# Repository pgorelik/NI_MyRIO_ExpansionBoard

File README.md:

# NI_MyRIO_ExpansionBoard
Breakout board with lick detection, solenoid driving and lights

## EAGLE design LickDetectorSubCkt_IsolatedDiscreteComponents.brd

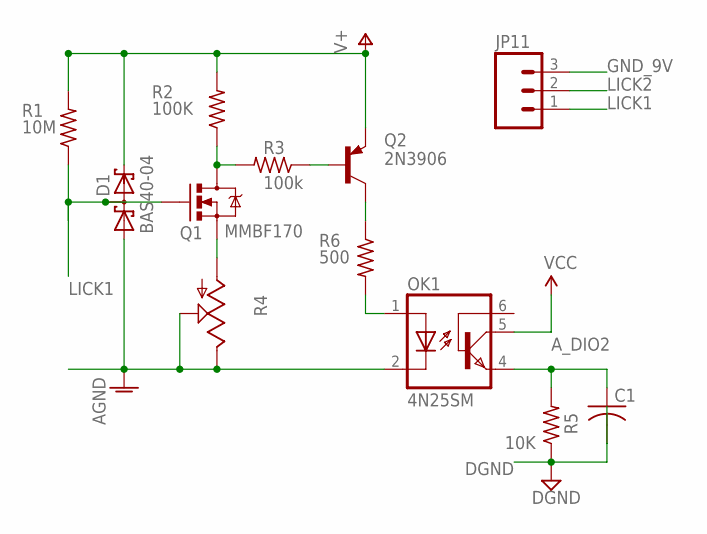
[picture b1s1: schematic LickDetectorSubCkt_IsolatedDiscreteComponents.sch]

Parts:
C1: C-US025-024X044; C025-024X044
D1: BAS40-04; SOT23
JP11: M03POLAR; MOLEX-1X3
OK1: 4N25SM; DIL6-SMD
Q1: MMBF170; SOT23-3
Q2: 2N3906; SOT23-BEC
R1: 10M; 0805S
R2: 100K; 0805S
R3: 100k; 0805S
R4: TRIM_US-B25P; B25P
R5: 10K; 0805S
R6: 500; 0805S

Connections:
AGND: D1.1 (A1), OK1.2 (C), R4.E, R4.S
A_DIO2: C1.1, OK1.4 (EMI), R5.2
DGND: C1.2, R5.1
GND_9V: JP11.3
LICK1: D1.3 (C1A2), JP11.1, Q1.1 (G), R1.1
LICK2: JP11.2
unnamed: Q1.2 (S), R4.A
unnamed: Q1.3 (D), R2.1, R3.2
unnamed: Q2.B, R3.1
unnamed: OK1.1 (A), R6.2
unnamed: Q2.C, R6.1
V+: D1.2 (C2), Q2.E, R1.2, R2.2
VCC: OK1.5 (COL)

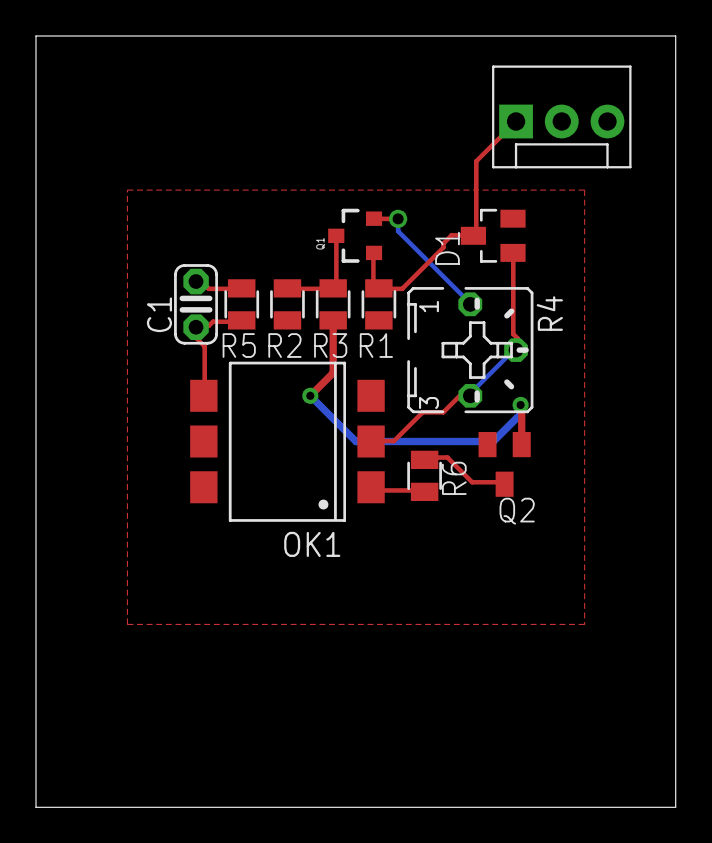
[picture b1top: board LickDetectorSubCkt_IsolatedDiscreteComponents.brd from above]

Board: 2 copper layers, 35.5 x 42.9 mm, 12 parts (0 on the bottom side), 10 nets.

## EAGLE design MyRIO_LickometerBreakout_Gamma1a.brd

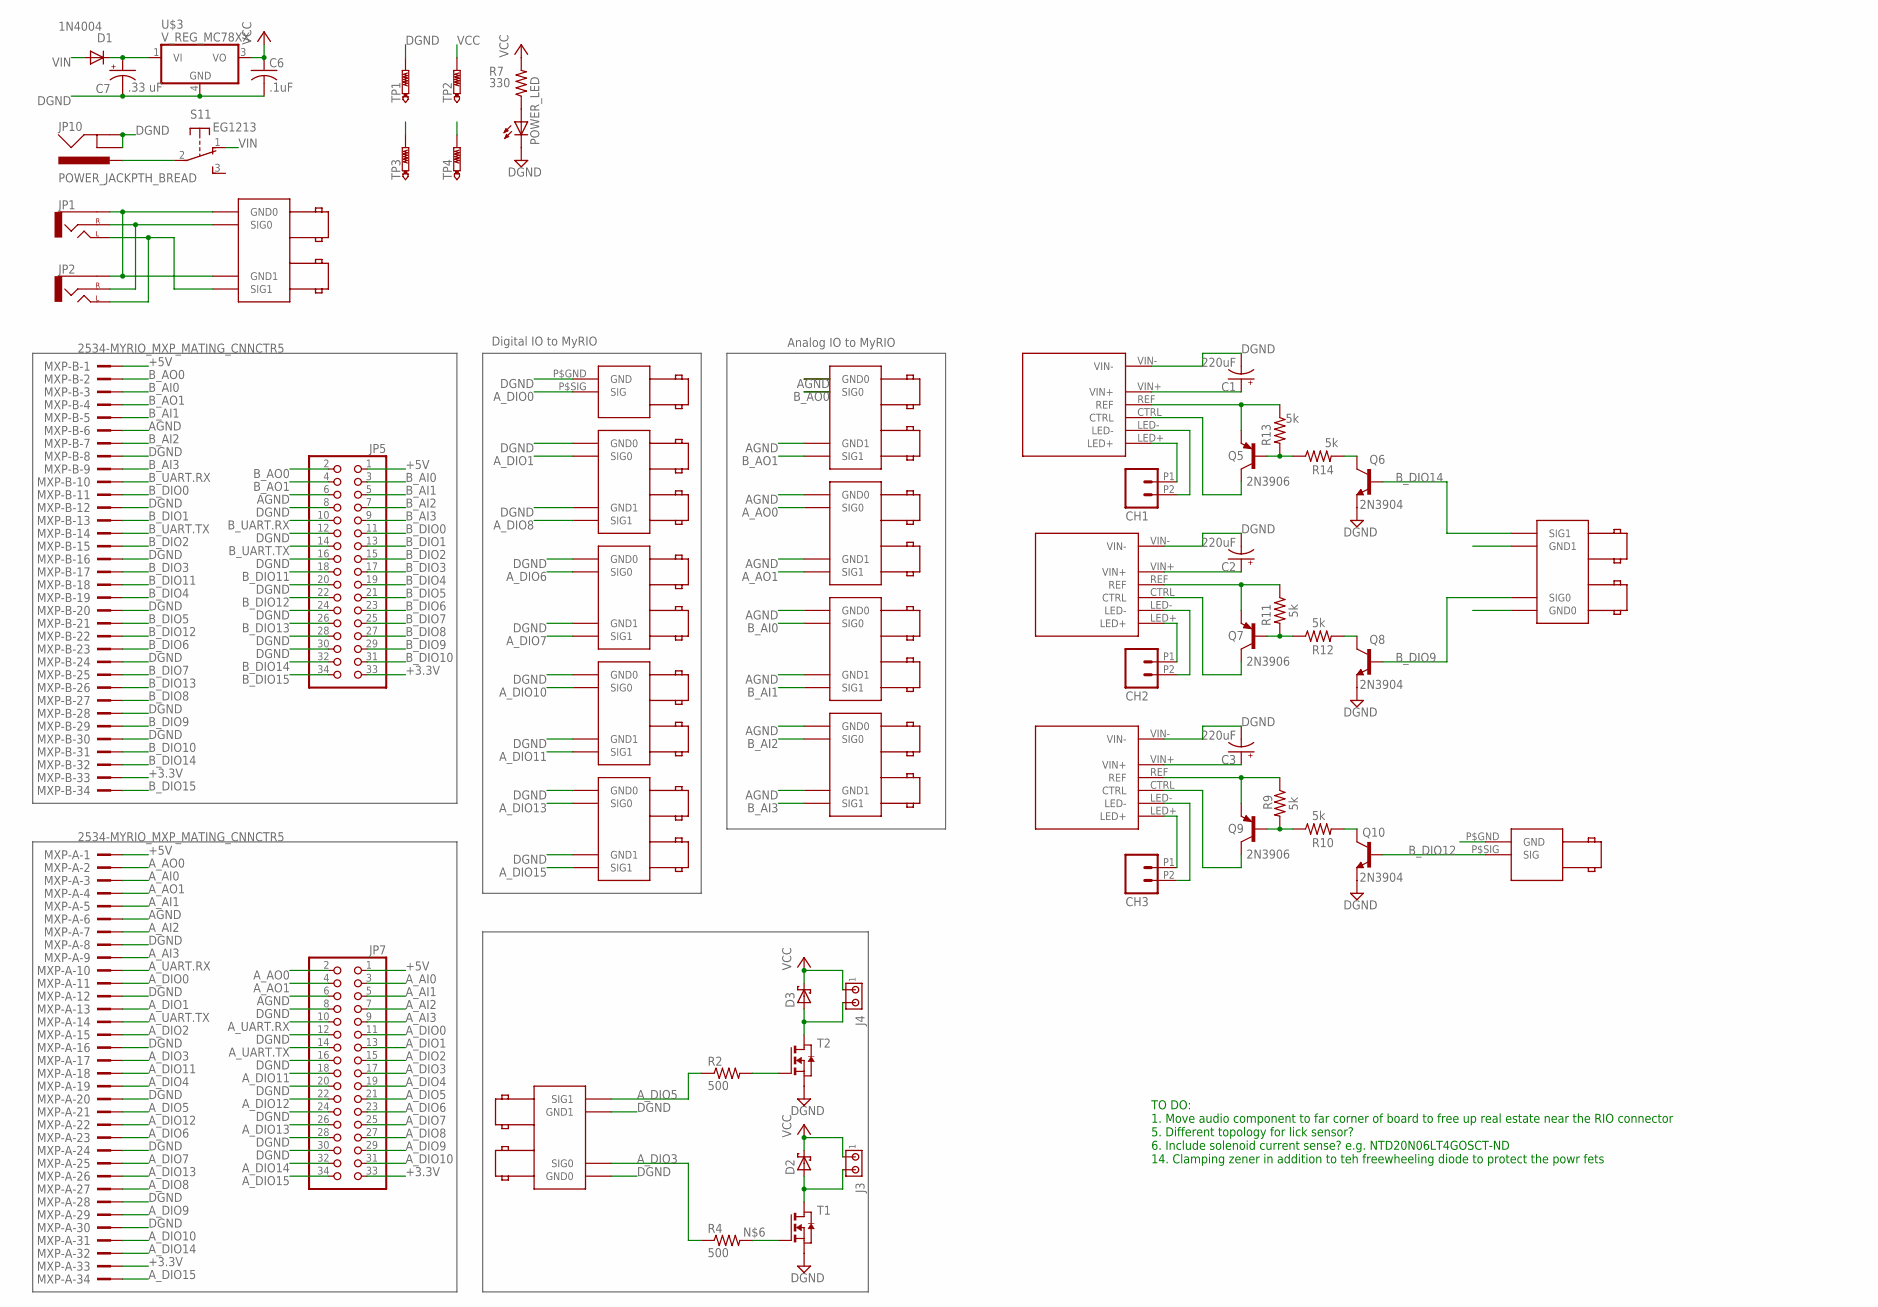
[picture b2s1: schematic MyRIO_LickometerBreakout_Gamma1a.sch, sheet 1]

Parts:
AAO_0,1: BNC_RIGHT_ANGLE_DOUBLE
ACTV_REC: BNC_RIGHT_ANGLE
AUDIO: BNC_RIGHT_ANGLE_DOUBLE
BAI_0,1, BAI_2,3: BNC_RIGHT_ANGLE_DOUBLE
BAO_0,1: BNC_RIGHT_ANGLE_DOUBLE
BUCKPUCK1, BUCKPUCK2, BUCKPUCK3: BUCKPUCK-350-I; BUCKPUCK_I
C1, C2, C3: 220uF; E5-10,5
C6: .1uF; C0805
C7: .33 uF; E2,5-5
CAMERA: BNC_RIGHT_ANGLE_DOUBLE
CH1, CH2, CH3: M022.54MM_SCREWTERM; 1X02_2.54_SCREWTERM
D1: 1N4004; DO41-10
D2, D3: SCHOTTKY-DIODE; DIODE_SMB
D_FREE1_2, D_FREE3_4: BNC_RIGHT_ANGLE_DOUBLE
J3, J4: MTA02-100; 10X02MTA
JP1, JP2: AUDIO-JACKPTH; AUDIO-JACK
JP5, JP7: PINHD-2X17; 2X17
JP10: POWER_JACKPTH_BREAD; POWER_JACK_PTH_BREAD
LED_CUE: BNC_RIGHT_ANGLE
LED_MASK: BNC_RIGHT_ANGLE_DOUBLE
MXP-A: 2534-MYRIO_MXP_MATING_CNNCTR5; PAK100/2500-5-34-MXP_CONNCTR
MXP-B: 2534-MYRIO_MXP_MATING_CNNCTR5; PAK100/2500-5-34-MXP_CONNCTR
POWER_LED: LED3MM
Q5, Q7, Q9: 2N3906; SOT23-BEC
Q6, Q8, Q10: 2N3904; SOT23-BEC
R2, R4: 500; M1206
R7: 330; 0805S
R9, R10, R11, R12, R13, R14: 5k; 0805S
S1: EG1213
SHUTTER: BNC_RIGHT_ANGLE_DOUBLE
SLN: BNC_RIGHT_ANGLE_DOUBLE
T1, T2: NMOSSOT223; SOT223
TP1, TP2, TP3, TP4: PTR1PAD1-17Y; P1-17Y
U$3: V_REG_MC78XX; DPAK

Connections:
+3.3V: JP5.33, JP7.33, MXP-A.33, MXP-B.33
+5V: JP5.1, JP7.1, MXP-A.1, MXP-B.1; also elsewhere on the board
+9V: TP4.TP; also elsewhere on the board
AGND: AAO_0,1.P$GND0 (GND0), AAO_0,1.P$GND1 (GND1), BAI_0,1.P$GND0 (GND0), BAI_0,1.P$GND1 (GND1), BAI_2,3.P$GND0 (GND0), BAI_2,3.P$GND1 (GND1), BAO_0,1.P$GND0 (GND0), BAO_0,1.P$GND1 (GND1), JP5.6, JP7.6, MXP-A.6, MXP-B.6
A_AI0: JP7.3, MXP-A.3
A_AI1: JP7.5, MXP-A.5
A_AI2: JP7.7, MXP-A.7
A_AI3: JP7.9, MXP-A.9
A_AO0: AAO_0,1.P$SIG0 (SIG0), JP7.2, MXP-A.2
A_AO1: AAO_0,1.P$SIG1 (SIG1), JP7.4, MXP-A.4
A_DIO0: ACTV_REC.P$SIG (SIG), JP7.11, MXP-A.11
A_DIO1: CAMERA.P$SIG0 (SIG0), JP7.13, MXP-A.13
A_DIO2: JP7.15, MXP-A.15; also elsewhere on the board
A_DIO3: JP7.17, MXP-A.17, R4.1, SLN.P$SIG0 (SIG0)
A_DIO4: JP7.19, MXP-A.19; also elsewhere on the board
A_DIO5: JP7.21, MXP-A.21, R2.1, SLN.P$SIG1 (SIG1)
A_DIO6: JP7.23, MXP-A.23, SHUTTER.P$SIG0 (SIG0)
A_DIO7: JP7.25, MXP-A.25, SHUTTER.P$SIG1 (SIG1)
A_DIO8: CAMERA.P$SIG1 (SIG1), JP7.27, MXP-A.27
A_DIO9: JP7.29, MXP-A.29
A_DIO10: D_FREE1_2.P$SIG0 (SIG0), JP7.31, MXP-A.31
A_DIO11: D_FREE1_2.P$SIG1 (SIG1), JP7.18, MXP-A.18
A_DIO12: JP7.22, MXP-A.22
A_DIO13: D_FREE3_4.P$SIG0 (SIG0), JP7.26, MXP-A.26
A_DIO14: JP7.32, MXP-A.32
A_DIO15: D_FREE3_4.P$SIG1 (SIG1), JP7.34, MXP-A.34
A_UART.RX: JP7.10, MXP-A.10
A_UART.TX: JP7.14, MXP-A.14
BCKPCK_CTRL2: Q8.C, R12.2
BCKPCK_CTRL3: Q10.C, R10.2
B_AI0: BAI_0,1.P$SIG0 (SIG0), JP5.3, MXP-B.3
B_AI1: BAI_0,1.P$SIG1 (SIG1), JP5.5, MXP-B.5
B_AI2: BAI_2,3.P$SIG0 (SIG0), JP5.7, MXP-B.7
B_AI3: BAI_2,3.P$SIG1 (SIG1), JP5.9, MXP-B.9
B_AO0: BAO_0,1.P$SIG0 (SIG0), JP5.2, MXP-B.2
B_AO1: BAO_0,1.P$SIG1 (SIG1), JP5.4, MXP-B.4
B_DIO0: JP5.11, MXP-B.11
B_DIO1: JP5.13, MXP-B.13
B_DIO2: JP5.15, MXP-B.15
B_DIO3: JP5.17, MXP-B.17
B_DIO4: JP5.19, MXP-B.19
B_DIO5: JP5.21, MXP-B.21
B_DIO6: JP5.23, MXP-B.23
B_DIO7: JP5.25, MXP-B.25
B_DIO8: JP5.27, MXP-B.27
B_DIO9: JP5.29, LED_MASK.P$SIG0 (SIG0), MXP-B.29, Q8.B
B_DIO10: JP5.31, MXP-B.31
B_DIO11: JP5.18, MXP-B.18
B_DIO12: JP5.22, LED_CUE.P$SIG (SIG), MXP-B.22, Q10.B
B_DIO13: JP5.26, MXP-B.26
B_DIO14: JP5.32, LED_MASK.P$SIG1 (SIG1), MXP-B.32, Q6.B
B_DIO15: JP5.34, MXP-B.34
B_UART.RX: JP5.10, MXP-B.10
B_UART.TX: JP5.14, MXP-B.14
CTRL1: BUCKPUCK1.CTRL, Q5.C
CTRL2: BUCKPUCK2.CTRL, Q7.C
CTRL3: BUCKPUCK3.CTRL, Q9.C
DGND: ACTV_REC.P$GND (GND), BUCKPUCK1.LED-, BUCKPUCK1.VIN-, BUCKPUCK2.LED-, BUCKPUCK2.VIN-, BUCKPUCK3.LED-, BUCKPUCK3.VIN-, C1.-, C2.-, C3.-, C6.2, C7.-, CAMERA.P$GND0 (GND0), CAMERA.P$GND1 (GND1), CH1.P2 (2), CH2.P2 (2), CH3.P2 (2), D_FREE1_2.P$GND0 (GND0), D_FREE1_2.P$GND1 (GND1), D_FREE3_4.P$GND0 (GND0), D_FREE3_4.P$GND1 (GND1), JP5.8, JP5.12, JP5.16, JP5.20, JP5.24, JP5.28, JP5.30, JP7.8, JP7.12, JP7.16, JP7.20, JP7.24, JP7.28, JP7.30, JP10.GND, JP10.GNDBREAK, LED_CUE.P$GND (GND), LED_MASK.P$GND0 (GND0), LED_MASK.P$GND1 (GND1), MXP-A.8, MXP-A.12, MXP-A.16, MXP-A.20, MXP-A.24, MXP-A.28, MXP-A.30, MXP-B.8, MXP-B.12, MXP-B.16, MXP-B.20, MXP-B.24, MXP-B.28, MXP-B.30, POWER_LED.K (C), Q6.E, Q8.E, Q10.E, SHUTTER.P$GND0 (GND0), SHUTTER.P$GND1 (GND1), SLN.P$GND0 (GND0), SLN.P$GND1 (GND1), T1.3 (S), T2.3 (S), TP1.TP, U$3.4 (GND); also elsewhere on the board
GND-ISO: TP3.TP; also elsewhere on the board
LED3+: BUCKPUCK3.LED+, CH3.P1 (1)
unnamed: R2.2, T2.1 (G)
unnamed: AUDIO.P$GND0 (GND0), AUDIO.P$GND1 (GND1), JP1.SLEEVE, JP2.SLEEVE
unnamed: AUDIO.P$SIG0 (SIG0), JP1.RING (RIGHT), JP2.RING (RIGHT)
unnamed: AUDIO.P$SIG1 (SIG1), JP1.TIP (LEFT), JP2.TIP (LEFT)
unnamed: R4.2, T1.1 (G)
unnamed: BUCKPUCK3.REF, Q9.E, R9.1
unnamed: BUCKPUCK1.LED+, CH1.P1 (1)
unnamed: Q9.B, R9.2, R10.1
unnamed: BUCKPUCK1.VIN+, BUCKPUCK2.VIN+, BUCKPUCK3.VIN+, C1.+, C2.+, C3.+, C7.+, D1.C, U$3.1 (VI)
unnamed: BUCKPUCK2.LED+, CH2.P1 (1)
unnamed: POWER_LED.A, R7.1
unnamed: BUCKPUCK1.REF, Q5.E, R13.1
unnamed: BUCKPUCK2.REF, Q7.E, R11.1
unnamed: Q5.B, R13.2, R14.1
unnamed: Q7.B, R11.2, R12.1
unnamed: JP10.PWR, S1.2
unnamed: Q6.C, R14.2
VCC: C6.1, D2.C (A), D3.C (A), J3.1, J4.1, R7.2, TP2.TP, U$3.3 (VO)
VIN: D1.A, S1.1 (O)
VOUT-1: D2.A (C), J3.2, T1.2 (D), T1.4 (D)
VOUT-2: D3.A (C), J4.2, T2.2 (D), T2.4 (D)

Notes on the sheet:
Digital IO to MyRIO
Analog IO to MyRIO
TO DO: 1. Move audio component to far corner of board to free up real estate near the RIO connector 5. Different topology for lick sensor? 6. Include solenoid current sense? e.g. NTD20N06LT4GOSCT-ND 14. Clamping zener in addition to teh freewheeling diode to protect the powr fets

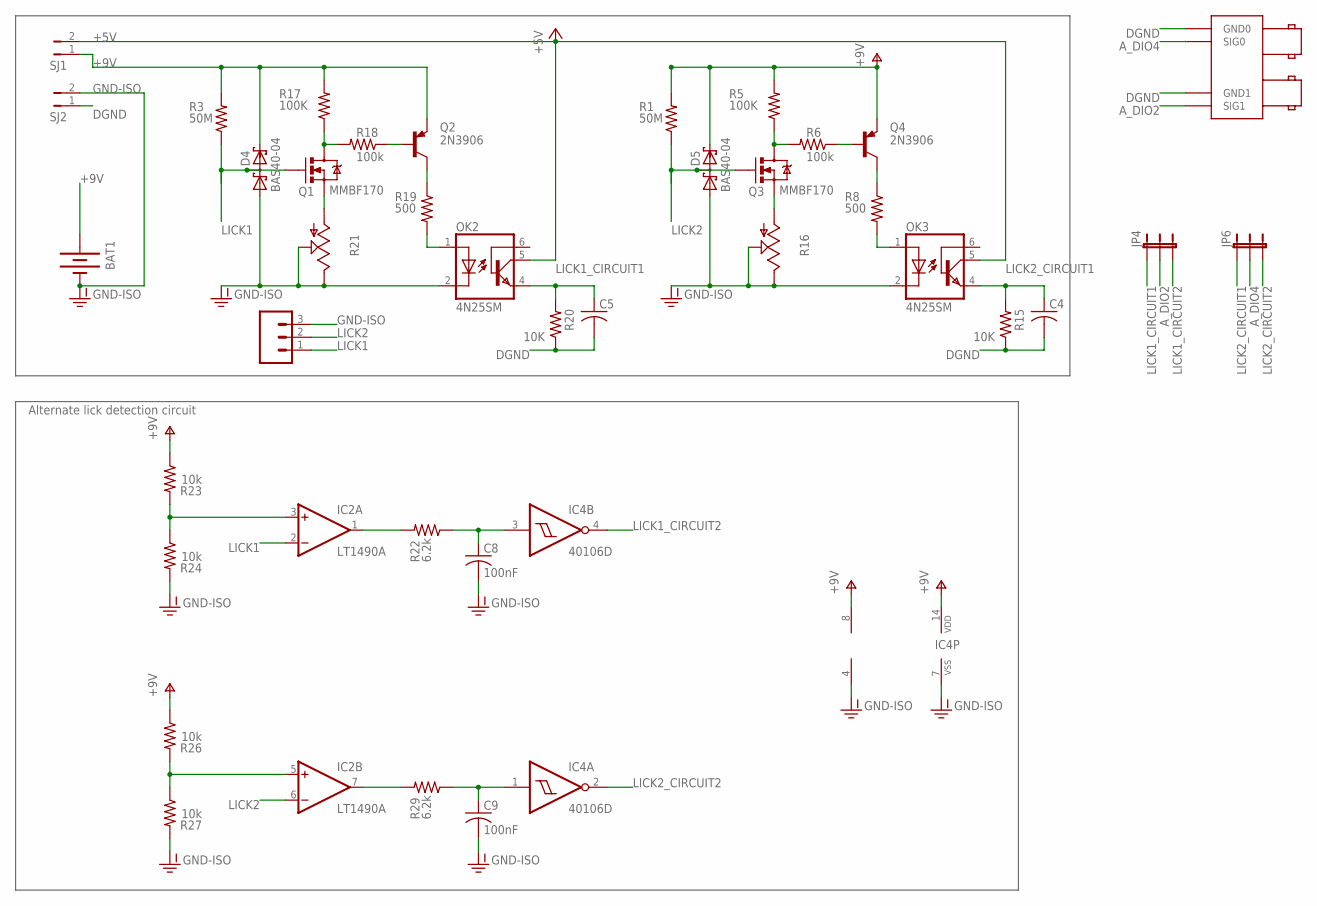
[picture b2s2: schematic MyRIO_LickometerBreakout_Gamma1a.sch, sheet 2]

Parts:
BAT1: BATTERY9V; BATTCON_9V
C4, C5: C-US025-024X044; C025-024X044
C8, C9: 100nF; C0805
D4, D5: BAS40-04; SOT23
IC2: LT1490A; SO08
IC4: 40106D; SO14
JP4, JP6: JUMPER-3PTH; 1X03
JP11: M03POLAR; MOLEX-1X3
LICK: BNC_RIGHT_ANGLE_DOUBLE
OK2, OK3: 4N25SM; DIL6-SMD
Q1, Q3: MMBF170; SOT23-3
Q2, Q4: 2N3906; SOT23-BEC
R1, R3: 50M; 0805S
R5, R17: 100K; 0805S
R6, R18: 100k; 0805S
R8, R19: 500; 0805S
R15, R20: 10K; 0805S
R16, R21: TRIM_US-B25P; B25P
R22, R29: 6.2k; 0805S
R23, R24, R26, R27: 10k; 0805S
SJ1, SJ2: JUMPER-PTH-2-NO; PTH-JUMPER-2-NO_NO_SILK

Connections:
+5V: OK2.5 (COL), OK3.5 (COL), SJ1.2; also elsewhere on the board
+9V: BAT1.+, D4.2 (C2), D5.2 (C2), IC2.8 (V+), IC4.14 (VDD), Q2.E, Q4.E, R1.2, R3.2, R5.2, R17.2, R23.1, R26.1, SJ1.1; also elsewhere on the board
A_DIO2: JP4.2, LICK.P$SIG1 (SIG1); also elsewhere on the board
A_DIO4: JP6.2, LICK.P$SIG0 (SIG0); also elsewhere on the board
DGND: C4.2, C5.2, LICK.P$GND0 (GND0), LICK.P$GND1 (GND1), R15.1, R20.1, SJ2.1; also elsewhere on the board
GND-ISO: BAT1.-, C8.2, C9.2, D4.1 (A1), D5.1 (A1), IC2.4 (V-), IC4.7 (VSS), JP11.3, OK2.2 (C), OK3.2 (C), R16.E, R16.S, R21.E, R21.S, R24.2, R27.2, SJ2.2; also elsewhere on the board
LICK1: D4.3 (C1A2), IC2.2 (-IN), JP11.1, Q1.1 (G), R3.1
LICK1_CIRCUIT1: C5.1, JP4.1, OK2.4 (EMI), R20.2
LICK1_CIRCUIT2: IC4.4 (O), JP4.3
LICK2: D5.3 (C1A2), IC2.6 (-IN), JP11.2, Q3.1 (G), R1.1
LICK2_CIRCUIT1: C4.1, JP6.1, OK3.4 (EMI), R15.2
LICK2_CIRCUIT2: IC4.2 (O), JP6.3
unnamed: Q1.3 (D), R17.1, R18.2
unnamed: Q3.3 (D), R5.1, R6.2
unnamed: Q4.B, R6.1
unnamed: OK3.1 (A), R8.2
unnamed: Q4.C, R8.1
unnamed: Q3.2 (S), R16.A
unnamed: Q2.B, R18.1
unnamed: OK2.1 (A), R19.2
unnamed: Q2.C, R19.1
unnamed: Q1.2 (S), R21.A
unnamed: C8.1, IC4.3 (I), R22.1
unnamed: IC2.1 (OUT), R22.2
unnamed: IC2.3 (+IN), R23.2, R24.1
unnamed: IC2.5 (+IN), R26.2, R27.1
unnamed: C9.1, IC4.1 (I), R29.1
unnamed: IC2.7 (OUT), R29.2

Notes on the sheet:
Alternate lick detection circuit

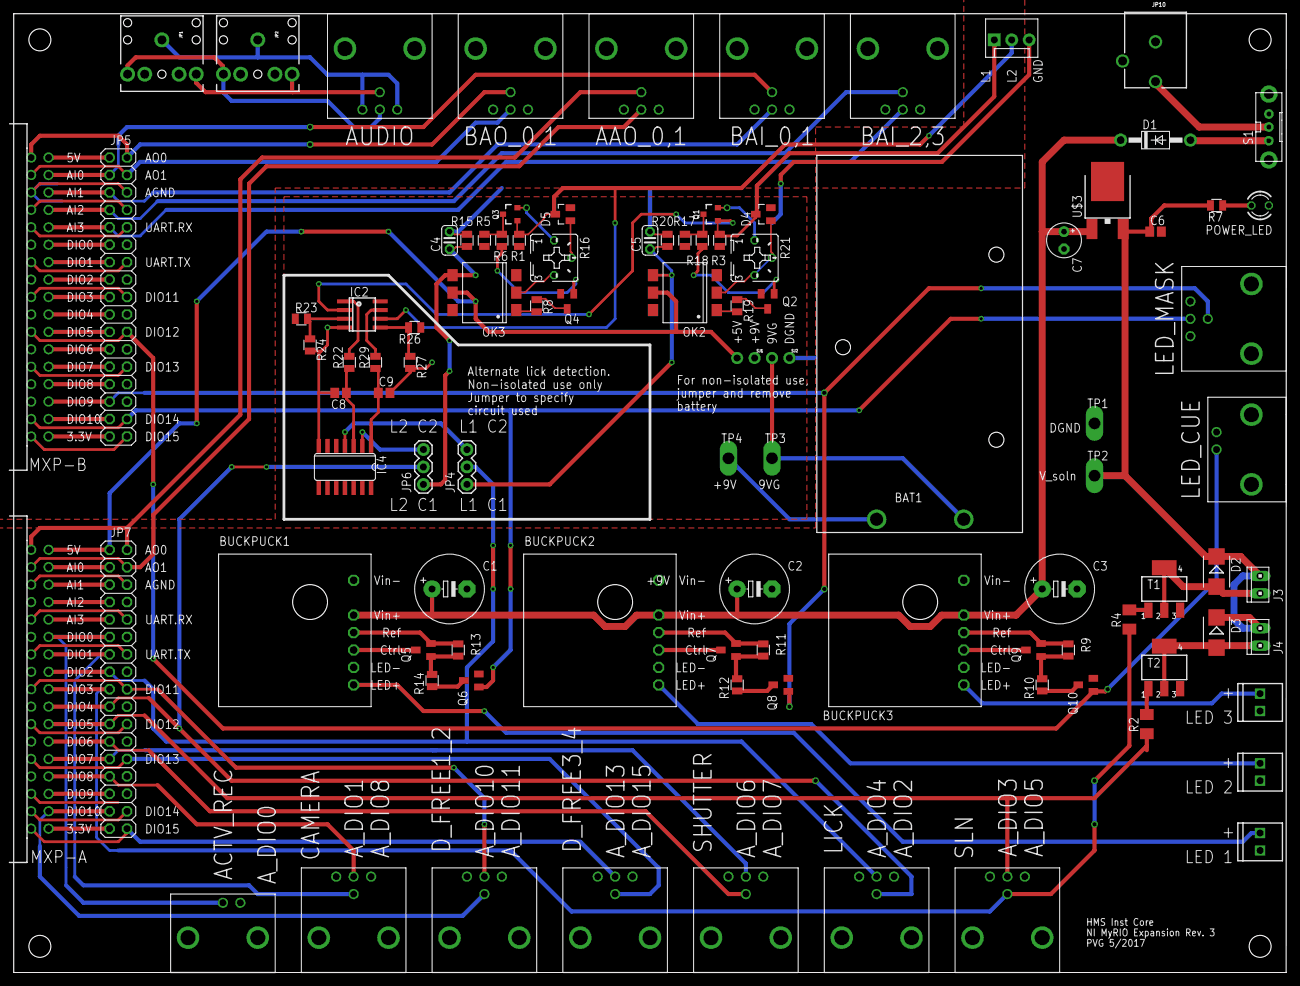
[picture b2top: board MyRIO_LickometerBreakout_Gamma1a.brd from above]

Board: 2 copper layers, 185.4 x 139.7 mm, 99 parts (0 on the bottom side), 103 nets.

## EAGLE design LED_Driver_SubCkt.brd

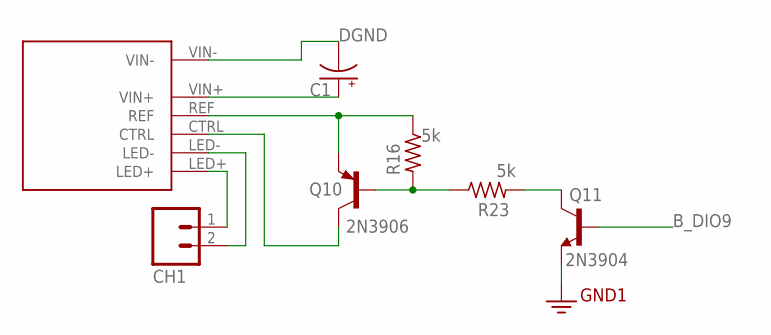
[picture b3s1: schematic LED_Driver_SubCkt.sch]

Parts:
BUCKPUCK1: BUCKPUCK-350-I; BUCKPUCK_I
C1: CPOL-USE5-10.5; E5-10,5
CH1: M023.5MM_LOCK; SCREWTERMINAL-3.5MM-2_LOCK
Q10: 2N3906; SOT23-BEC
Q11: 2N3904; SOT23-BEC
R16, R23: 5k; 0805S

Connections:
B_DIO9: Q11.B
CTRL1: BUCKPUCK1.CTRL, Q10.C
DGND: BUCKPUCK1.LED-, BUCKPUCK1.VIN-, C1.-, CH1.2, Q11.E
unnamed: BUCKPUCK1.LED+, CH1.1
unnamed: BUCKPUCK1.VIN+, C1.+
unnamed: BUCKPUCK1.REF, Q10.E, R16.1
unnamed: Q10.B, R16.2, R23.1
unnamed: Q11.C, R23.2

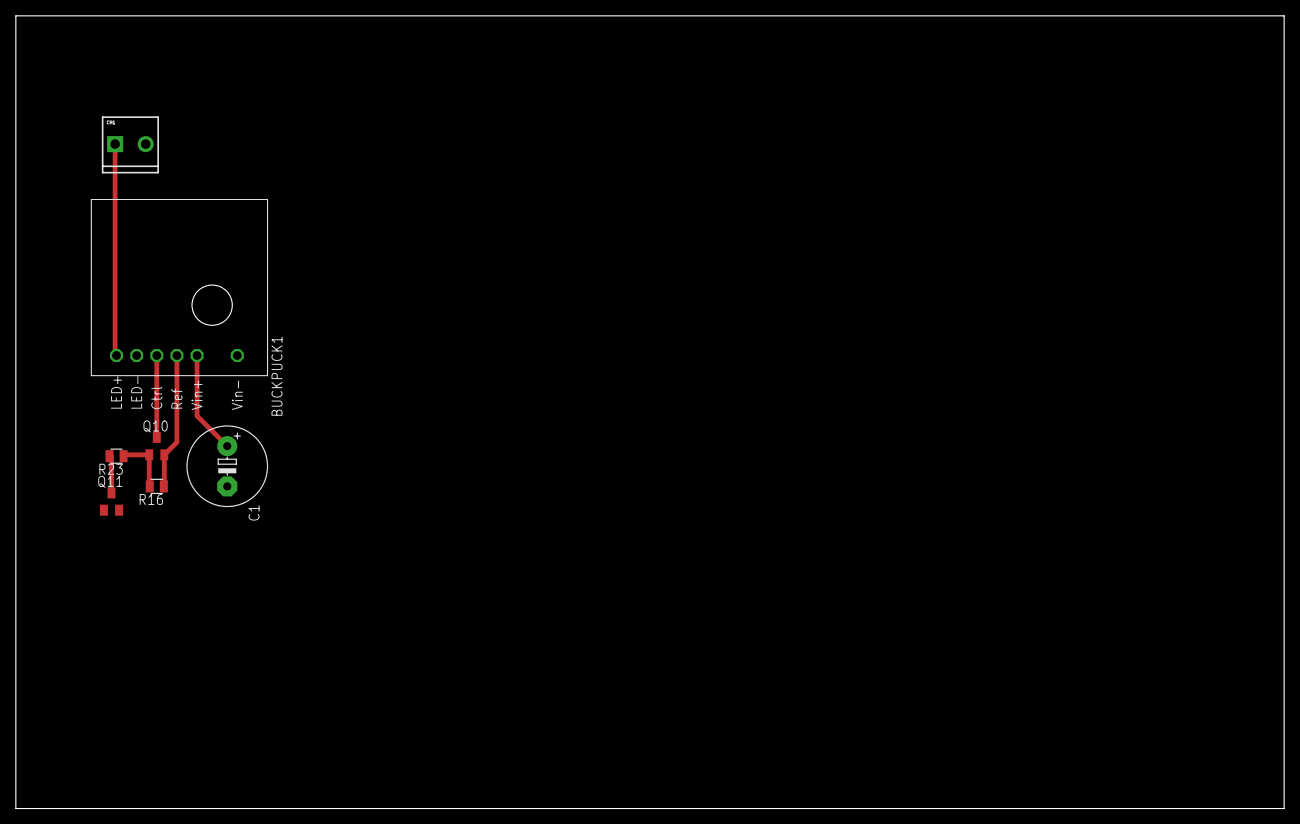
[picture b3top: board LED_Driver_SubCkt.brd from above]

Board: 2 copper layers, 160.0 x 100.0 mm, 7 parts (0 on the bottom side), 7 nets.

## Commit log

2017-06-01 Initial upload
    Includes the main board and sub-components for LED driving and lick detection
2018-10-16 Create PCB-Eagle
2018-10-16 Create test

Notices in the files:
parts and their libraries:
Pavel-PowerIC: Licensing: Creative Commons ShareAlike 4.0 International - https://creativecommons.org/licenses/by-sa/4.0
